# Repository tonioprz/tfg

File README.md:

# tfg

Trabajo de fin de grado realizado por Antonio Pérez García

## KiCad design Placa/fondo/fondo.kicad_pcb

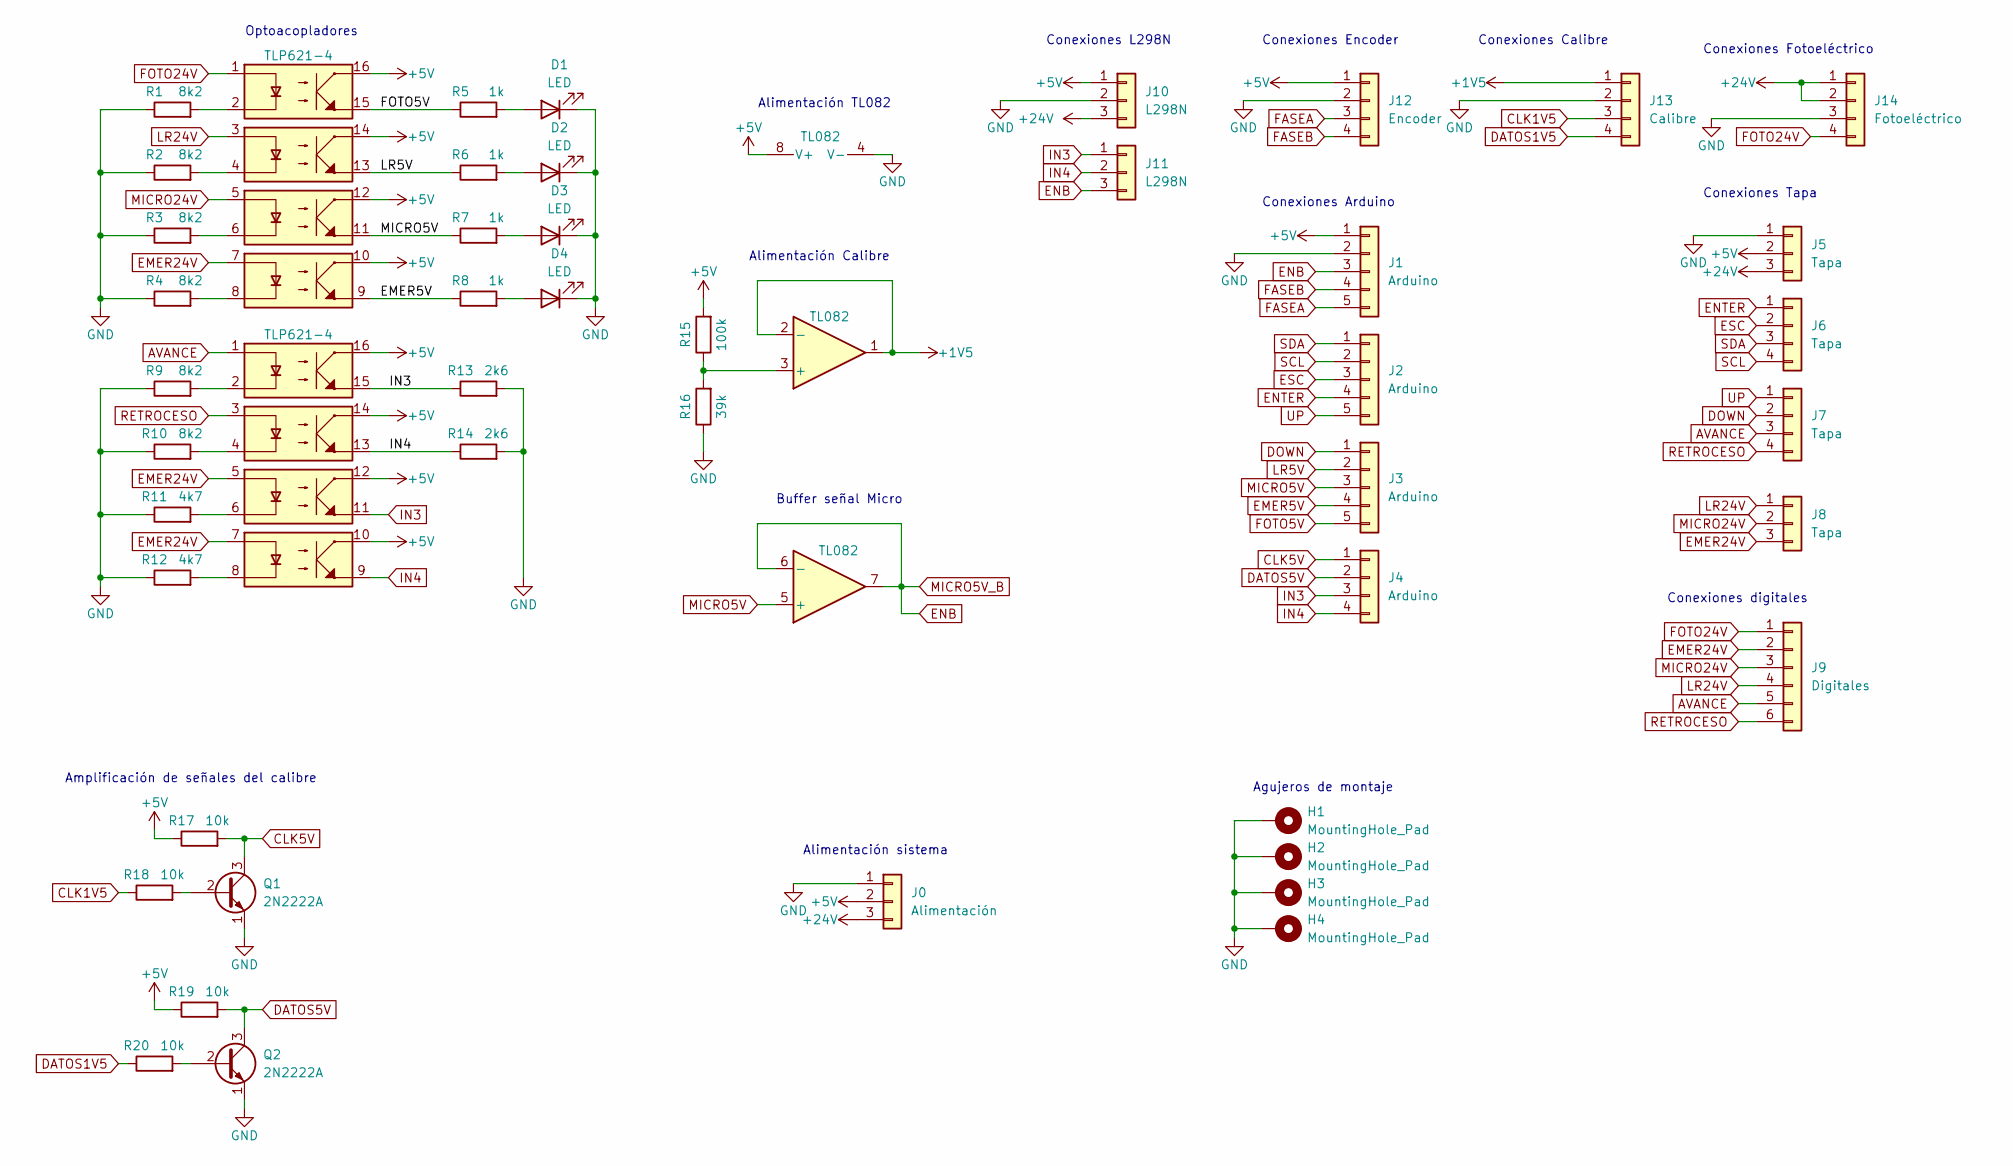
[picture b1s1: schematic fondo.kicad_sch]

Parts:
D1, D2, D3, D4: LED; LED_D3.0mm
H1, H2, H3, H4: MountingHole_Pad; MountingHole_3.2mm_M3_DIN965_Pad
J0: Alimentación; TerminalBlock_bornier-3_P5.08mm
J1, J2, J3: Arduino; TerminalBlock_TE_282834-5_1x05_P2.54mm_Horizontal
J4: Arduino; TerminalBlock_TE_282834-4_1x04_P2.54mm_Horizontal
J5, J8: Tapa; TerminalBlock_TE_282834-3_1x03_P2.54mm_Horizontal
J6, J7: Tapa; TerminalBlock_TE_282834-4_1x04_P2.54mm_Horizontal
J9: Digitales; TerminalBlock_TE_282834-6_1x06_P2.54mm_Horizontal
J10: L298N; TerminalBlock_bornier-3_P5.08mm
J11: L298N; TerminalBlock_TE_282834-3_1x03_P2.54mm_Horizontal
J12: Encoder; TerminalBlock_TE_282834-4_1x04_P2.54mm_Horizontal
J13: Calibre; TerminalBlock_TE_282834-4_1x04_P2.54mm_Horizontal
J14: Fotoeléctrico; TerminalBlock_TE_282834-4_1x04_P2.54mm_Horizontal
Q1, Q2: 2N2222A; TO-92
R1, R2, R3, R4, R9, R10: 8k2; R_Axial_DIN0207_L6.3mm_D2.5mm_P10.16mm_Horizontal
R5, R6, R7, R8: 1k; R_Axial_DIN0207_L6.3mm_D2.5mm_P10.16mm_Horizontal
R11, R12: 4k7; R_Axial_DIN0207_L6.3mm_D2.5mm_P10.16mm_Horizontal
R13, R14: 2k6; R_Axial_DIN0207_L6.3mm_D2.5mm_P10.16mm_Horizontal
R15: 100k; R_Axial_DIN0207_L6.3mm_D2.5mm_P10.16mm_Horizontal
R16: 39k; R_Axial_DIN0207_L6.3mm_D2.5mm_P10.16mm_Horizontal
R17, R18, R19, R20: 10k; R_Axial_DIN0207_L6.3mm_D2.5mm_P10.16mm_Horizontal
U1, U2: TLP621-4; DIP-16_W10.16mm
U3: TL082; DIP-8_W7.62mm

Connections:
+1V5: J13.1, U3.1, U3.2 (-)
+5V: J0.2, J1.1, J5.2, J10.1, J12.1, R15.2, R17.1, R19.1, U1.10, U1.12, U1.14, U1.16, U2.10, U2.12, U2.14, U2.16, U3.8 (V+)
+24V: J0.3, J5.3, J10.3, J14.1, J14.2
AVANCE: J7.3, J9.5, U2.1
CLK1V5: J13.3, R18.1
CLK5V: J4.1, Q1.3 (C), R17.2
DATOS1V5: J13.4, R20.1
DATOS5V: J4.2, Q2.3 (C), R19.2
DOWN: J3.1, J7.2
EMER5V: J3.4, R8.1, U1.9
EMER24V: J8.3, J9.2, U1.7, U2.5, U2.7
ENB: J1.3, J11.3, U3.6 (-), U3.7
ENTER: J2.4, J6.1
ESC: J2.3, J6.2
FASEA: J1.5, J12.3
FASEB: J1.4, J12.4
FOTO5V: J3.5, R5.1, U1.15
FOTO24V: J9.1, J14.4, U1.1
GND: D1.1 (K), D2.1 (K), D3.1 (K), D4.1 (K), H1.1, H2.1, H3.1, H4.1, J0.1, J1.2, J5.1, J10.2, J12.2, J13.2, J14.3, Q1.1 (E), Q2.1 (E), R1.1, R2.1, R3.1, R4.1, R9.1, R10.1, R11.1, R12.1, R13.2, R14.2, R16.1, U3.4 (V-)
IN3: J4.3, J11.1, R13.1, U2.11, U2.15
IN4: J4.4, J11.2, R14.1, U2.9, U2.13
LR5V: J3.2, R6.1, U1.13
LR24V: J8.1, J9.4, U1.3
MICRO5V: J3.3, R7.1, U1.11, U3.5 (+)
MICRO24V: J8.2, J9.3, U1.5
unnamed: Q1.2 (B), R18.2
unnamed: Q2.2 (B), R20.2
unnamed: R1.2, U1.2
unnamed: R2.2, U1.4
unnamed: R3.2, U1.6
unnamed: R4.2, U1.8
unnamed: D1.2 (A), R5.2
unnamed: D2.2 (A), R6.2
unnamed: D3.2 (A), R7.2
unnamed: D4.2 (A), R8.2
unnamed: R9.2, U2.2
unnamed: R10.2, U2.4
unnamed: R11.2, U2.6
unnamed: R12.2, U2.8
unnamed: R15.1, R16.2, U3.3 (+)
RETROCESO: J7.4, J9.6, U2.3
SCL: J2.2, J6.4
SDA: J2.1, J6.3
UP: J2.5, J7.1

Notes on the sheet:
Conexiones Fotoeléctrico
Conexiones L298N
Conexiones Tapa
Amplificación de señales del calibre
Alimentación TL082
Buffer señal Micro
Alimentación Calibre
Optoacopladores
Alimentación sistema
Conexiones Calibre
Conexiones digitales
Conexiones Arduino
Agujeros de montaje
Conexiones Encoder

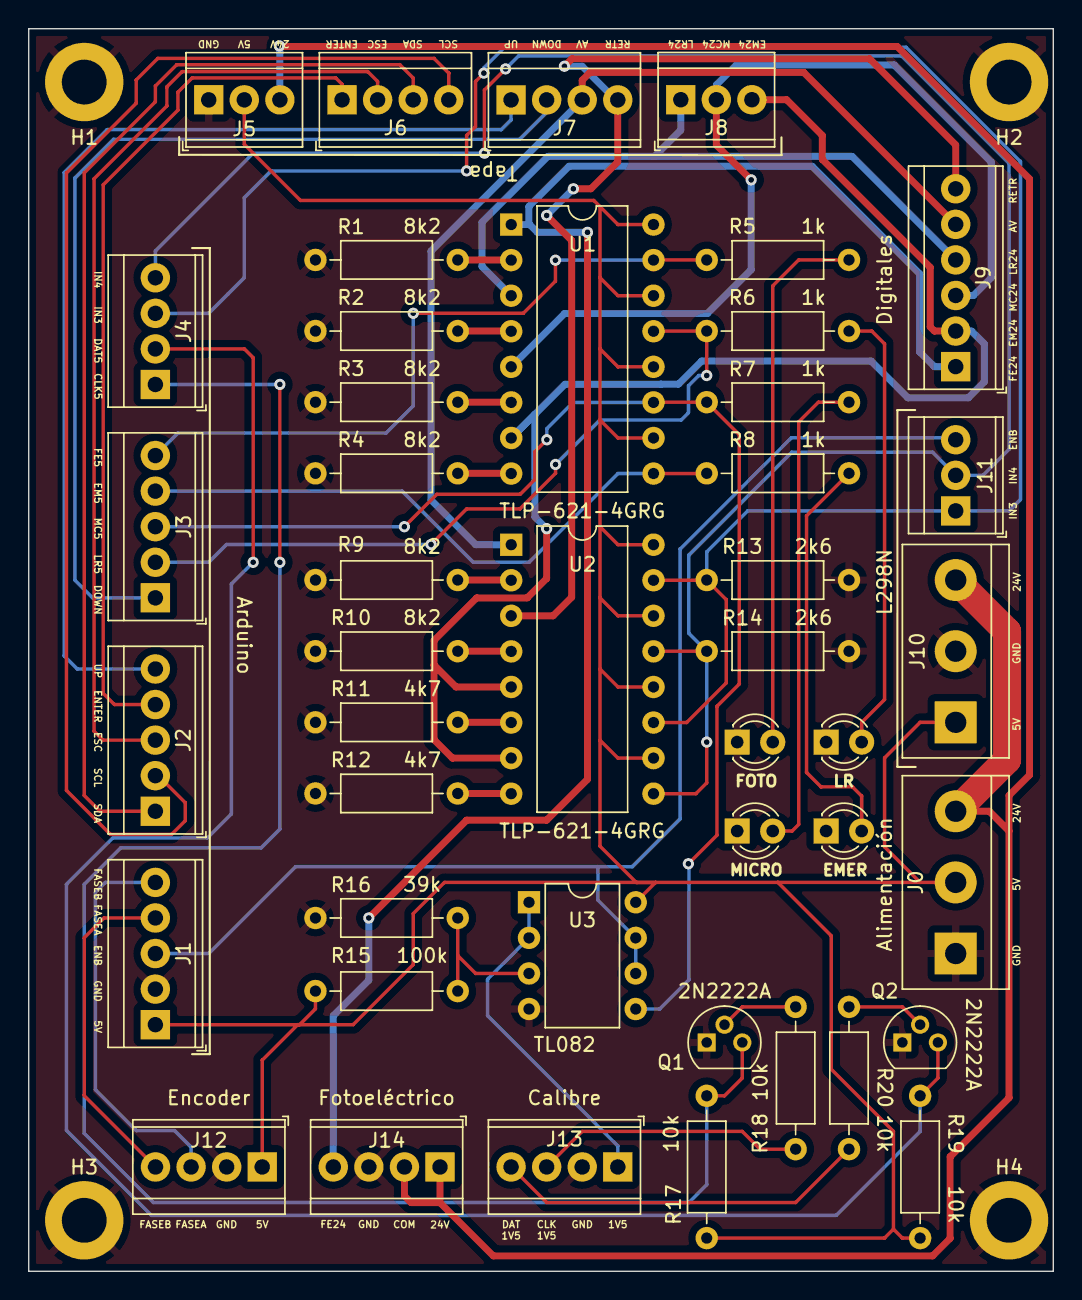
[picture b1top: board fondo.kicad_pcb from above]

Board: 2 copper layers, 73.2 x 88.7 mm, 48 parts (0 on the bottom side), 44 nets.

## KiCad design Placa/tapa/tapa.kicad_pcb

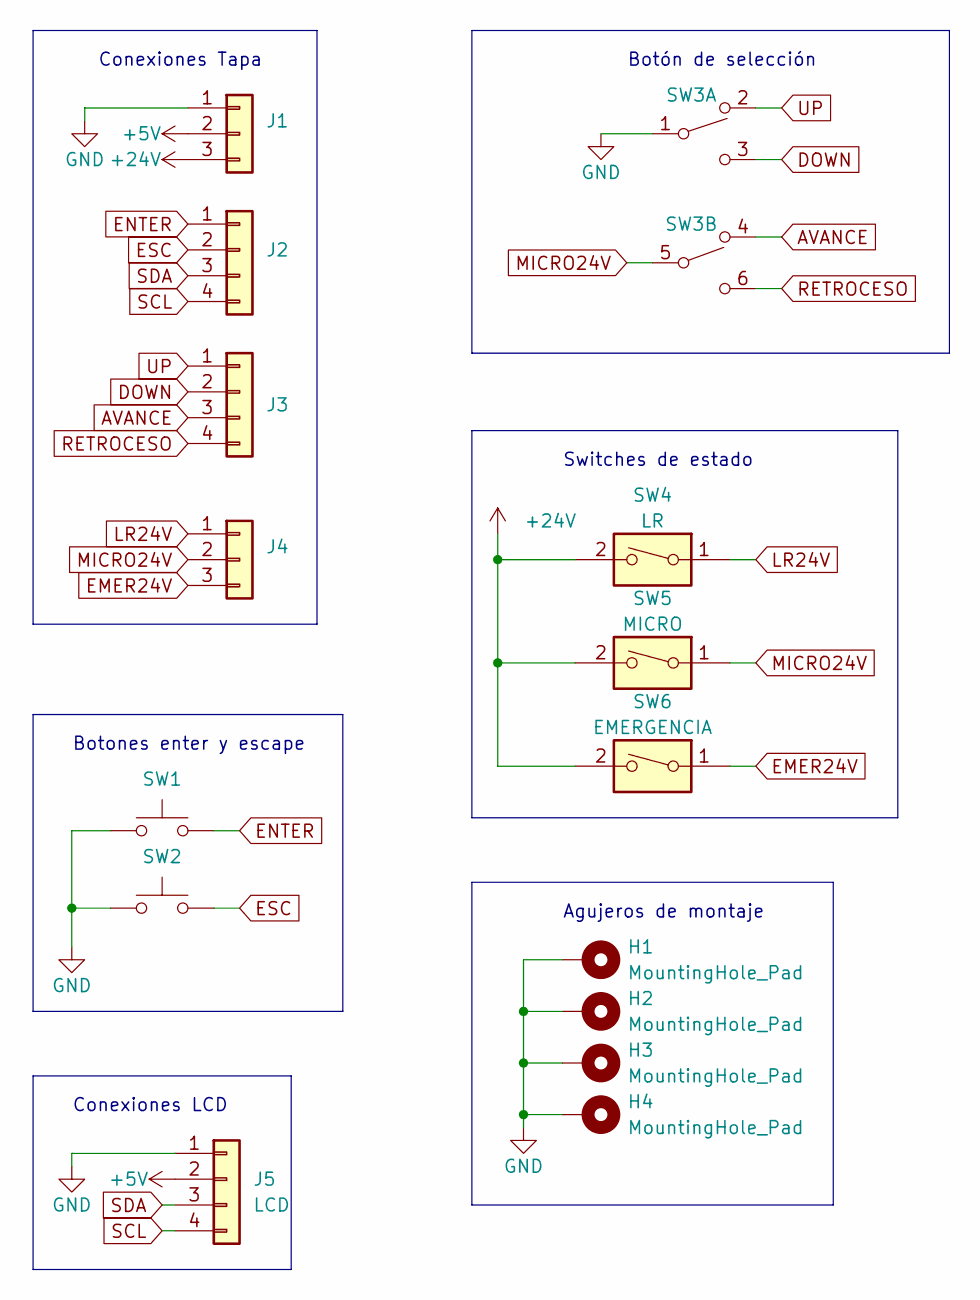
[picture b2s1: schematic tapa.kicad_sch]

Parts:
H1, H2, H3, H4: MountingHole_Pad; MountingHole_3.2mm_M3_DIN965_Pad
J1, J4: Conn_01x03; TerminalBlock_TE_282834-3_1x03_P2.54mm_Horizontal
J2, J3: Conn_01x04; TerminalBlock_TE_282834-4_1x04_P2.54mm_Horizontal
J5: LCD; TerminalBlock_TE_282834-4_1x04_P2.54mm_Horizontal
SW1: Enter; SW_PUSH_6mm_H8mm
SW2: ESC; SW_PUSH_6mm_H8mm
SW3: Botón Selección; TerminalBlock_TE_282834-6_1x06_P2.54mm_Horizontal
SW4: LR; TerminalBlock_TE_282834-2_1x02_P2.54mm_Horizontal
SW5: MICRO; TerminalBlock_TE_282834-2_1x02_P2.54mm_Horizontal
SW6: EMERGENCIA; TerminalBlock_TE_282834-2_1x02_P2.54mm_Horizontal

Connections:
+5V: J1.2, J5.2
+24V: J1.3, SW4.2, SW5.2, SW6.2
AVANCE: J3.3, SW3.4 (A)
DOWN: J3.2, SW3.3 (C)
EMER24V: J4.3, SW6.1
ENTER: J2.1, SW1.2
ESC: J2.2, SW2.2
GND: H1.1, H2.1, H3.1, H4.1, J1.1, J5.1, SW1.1, SW2.1, SW3.1 (B)
LR24V: J4.1, SW4.1
MICRO24V: J4.2, SW3.5 (B), SW5.1
RETROCESO: J3.4, SW3.6 (C)
SCL: J2.4, J5.4
SDA: J2.3, J5.3
UP: J3.1, SW3.2 (A)

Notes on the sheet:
Botones enter y escape
Botón de selección
Conexiones LCD
Agujeros de montaje
Conexiones Tapa
Switches de estado

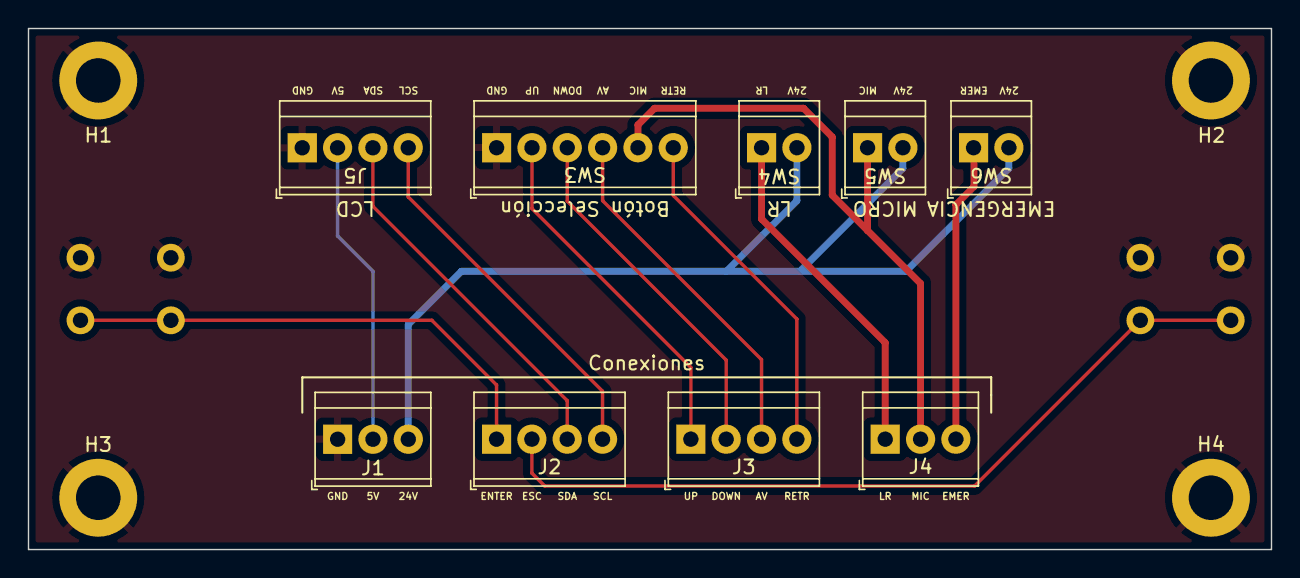
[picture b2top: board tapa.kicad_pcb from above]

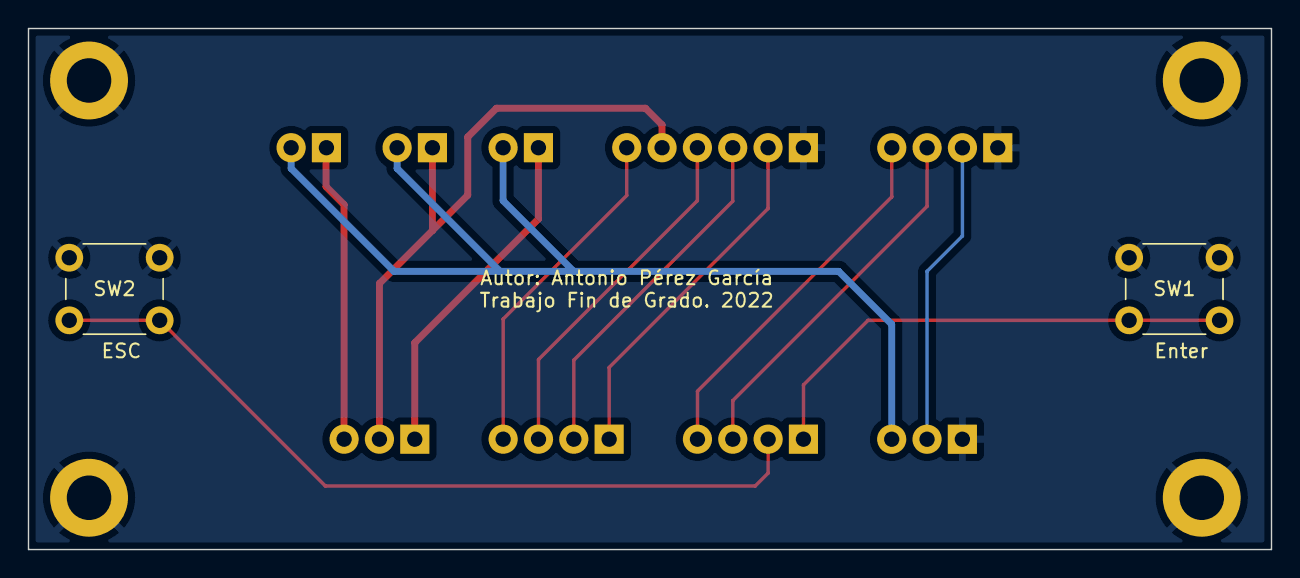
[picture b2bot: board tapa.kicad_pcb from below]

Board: 2 copper layers, 89.4 x 37.5 mm, 15 parts (2 on the bottom side), 14 nets.

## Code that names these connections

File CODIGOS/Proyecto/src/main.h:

#define faseA 2
#define faseB 3


#define BUTTON_ESC 22
#define BUTTON_ENTER 23
#define BUTTON_UP 24
#define BUTTON_DOWN 25

#define ENB 5
#define IN3 27
#define IN4 26

bool enter;
bool esc;
bool up;
bool down;
bool esc_ant = 0;
bool enter_ant = 0;
bool up_ant = 0;
bool down_ant = 0;

long posicion = 0;
long * pposicion = &posicion;

char state = 'i';
bool discreto = 0;
long desplazamiento = 10000;
long objetivo = 0;

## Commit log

2020-12-20 Commit inicial
2020-12-21 Pruebas switch
2021-10-19 Reset
2021-10-19 LiquidCrystal
2021-10-20 OUTPUT motor
2021-10-20 Interrupciones encoder
2021-10-21 Primeros estados
2021-10-23 Movimiento básico
2021-10-23 Clase Motor
2021-10-24 Cambio nombre carpeta
2021-10-24 Intento de Emergencia
2021-10-25 Librería Ethernet y movimiento a include
2021-10-25 Emergencia en clase motor
2021-10-25 Añadido esquema
2021-10-26 Actualizados valores a motor del laboratorio
2021-10-29 Medidas esquema
2022-02-01 Case emergencia y sin micro
2022-02-02 Pruebas Ethernet
2022-02-14 Calibre funcionando
2022-02-14 Reorganización carpetas
2022-02-14 Inicio implementación TCP
2022-02-15 Envio de datos a RobotStudio
2022-02-15 Documentación Pinout y Estados
2022-02-15 Reorganización memoria
2022-02-15 Formato TFG ETSI
2022-02-15 Modificaciones memoria
2022-02-15 Archivos .tex de cada apartado
2022-02-16 Cambio nombre a main
2022-02-17 Introducción
2022-02-17 Corregido error signo en distancias largas
2022-02-18 Esquemas kicad
2022-02-21 Diseño de placa
2022-02-23 Finalización placas
2022-02-23 Borrado archivos innecesarios RobotStudio
2022-03-03 Medidas Caja
2022-03-21 Cambios menores
2022-04-11 Orden apartados
2022-04-19 Modos funcionamiento
2022-04-25 Secciones Hardware
2022-05-09 Hardware Arduino
2022-05-09 Cambios Hardware
2022-05-10 encoder
2022-05-10 lcd hardware
2022-05-11 Placa
2022-05-11 Comienzo placa optoacopladores
2022-05-12 Calibre comenzado
2022-05-16 Conversión a Arduino IDE
2022-05-16 listado señales
2022-05-18 Fin optoacopladores
2022-05-23 Dinámicas cinta configuradas
2022-05-31 imágenes placas
2022-05-31 placa tapa
2022-05-31 fin capitulo 3
2022-05-31 inicio caja
2022-06-01 imágenes caja
2022-06-14 base caja
2022-06-17 tapa
2022-06-22 Comienzo código arduino
2022-06-24 codigo arduino y diagrama
2022-06-28 diagrama
2022-06-28 fin arduino
2022-06-29 robotstudio sin micro
2022-06-29 correcciones 1
2022-06-30 correcciones 2
2022-06-30 notacion1
2022-07-01 fin robotstudio
2022-07-03 resumen
2022-07-03 pre-final
2022-07-03 resumen bien
2022-07-03 resultados
2022-07-03 conclusiones
2022-07-03 abstract
2022-07-06 creación guía de uso
2022-07-07 introducción mejorada
2022-07-07 correcciones
2022-07-07 comienzo de guia de uso
2022-07-09 casi final ya
2022-07-10 FINAL
2022-07-19 cambios postfinal
2022-07-19 archivos
